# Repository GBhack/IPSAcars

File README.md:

# IPSAcars : Evolution de véhicules autonomes dans un environnement urbain intelligent

## Description du projet :
Réalisation une maquette simulant un environement urbain comprenant des feux de signalisation "intelligents" (c´est à dire s´adaptant à la circulation) à l´ aide d´ une carte FPGA et, dans le même temps, des véhicules autonomes (à l´ aide d'un BeagleBone) capables de circuler dans cet environnement.

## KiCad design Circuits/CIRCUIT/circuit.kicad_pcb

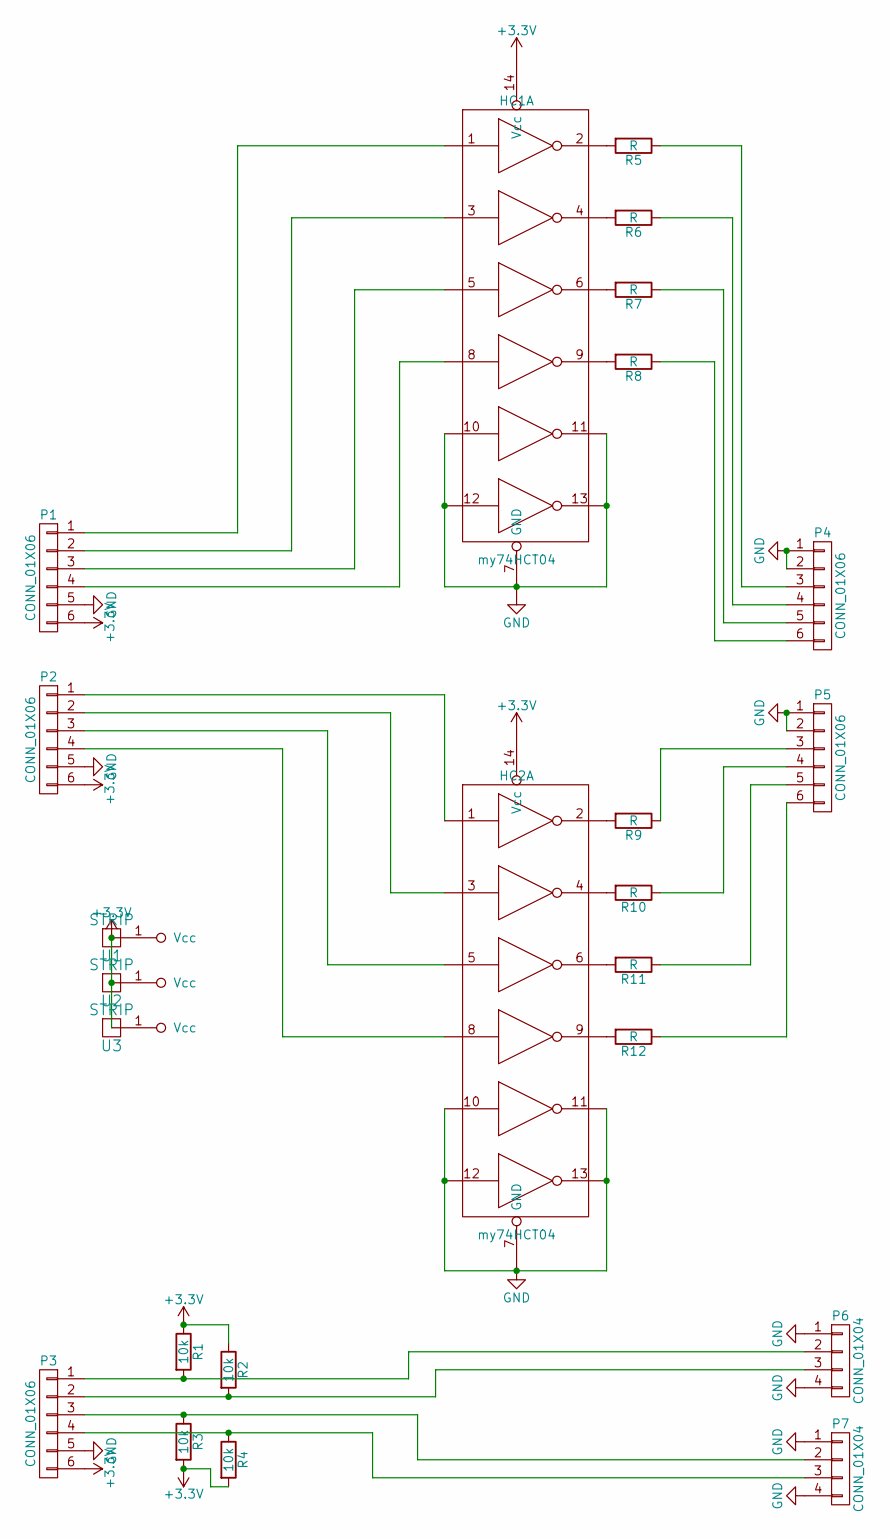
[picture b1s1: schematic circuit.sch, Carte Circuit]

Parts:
HC1, HC2: my74HCT04; DIP-14_W7.62mm
P1, P2, P3, P4, P5: CONN_01X06; Pin_Header_Angled_1x06
P6, P7: CONN_01X04; Pin_Header_Straight_1x04
R1, R2, R3, R4: 10k; Resistor_Horizontal_RM7mm
R5, R6, R7, R8, R9, R10, R11, R12: R; Resistor_Horizontal_RM7mm
U1, U2, U3: STRIP; SolderWirePad_2x_1-2mmDrill

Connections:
GND: HC1.7 (GND), HC2.7 (GND), HC2.10, HC2.11, HC2.12, HC2.13, P1.5, P2.5, P3.5, P4.1, P4.2, P5.1, P5.2, P6.1, P6.4, P7.1, P7.4
unnamed: HC1.1, P1.1
unnamed: HC1.2, R5.2
unnamed: HC1.3, P1.2
unnamed: HC1.4, R6.2
unnamed: HC1.5, P1.3
unnamed: HC1.6, R7.2
unnamed: HC1.8, P1.4
unnamed: HC1.9, R8.2
unnamed: HC1.10, HC1.11, HC1.12, HC1.13
unnamed: HC2.1, P2.1
unnamed: HC2.2, R9.2
unnamed: HC2.3, P2.2
unnamed: HC2.4, R10.2
unnamed: HC2.5, P2.3
unnamed: HC2.6, R11.2
unnamed: HC2.8, P2.4
unnamed: HC2.9, R12.2
unnamed: P3.1, P6.2, R1.2
unnamed: P3.2, P6.3, R2.2
unnamed: P3.3, P7.2, R3.1
unnamed: P3.4, P7.3, R4.1
unnamed: P4.3, R5.1
unnamed: P4.4, R6.1
unnamed: P4.5, R7.1
unnamed: P4.6, R8.1
unnamed: P5.3, R9.1
unnamed: P5.4, R10.1
unnamed: P5.5, R11.1
unnamed: P5.6, R12.1

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
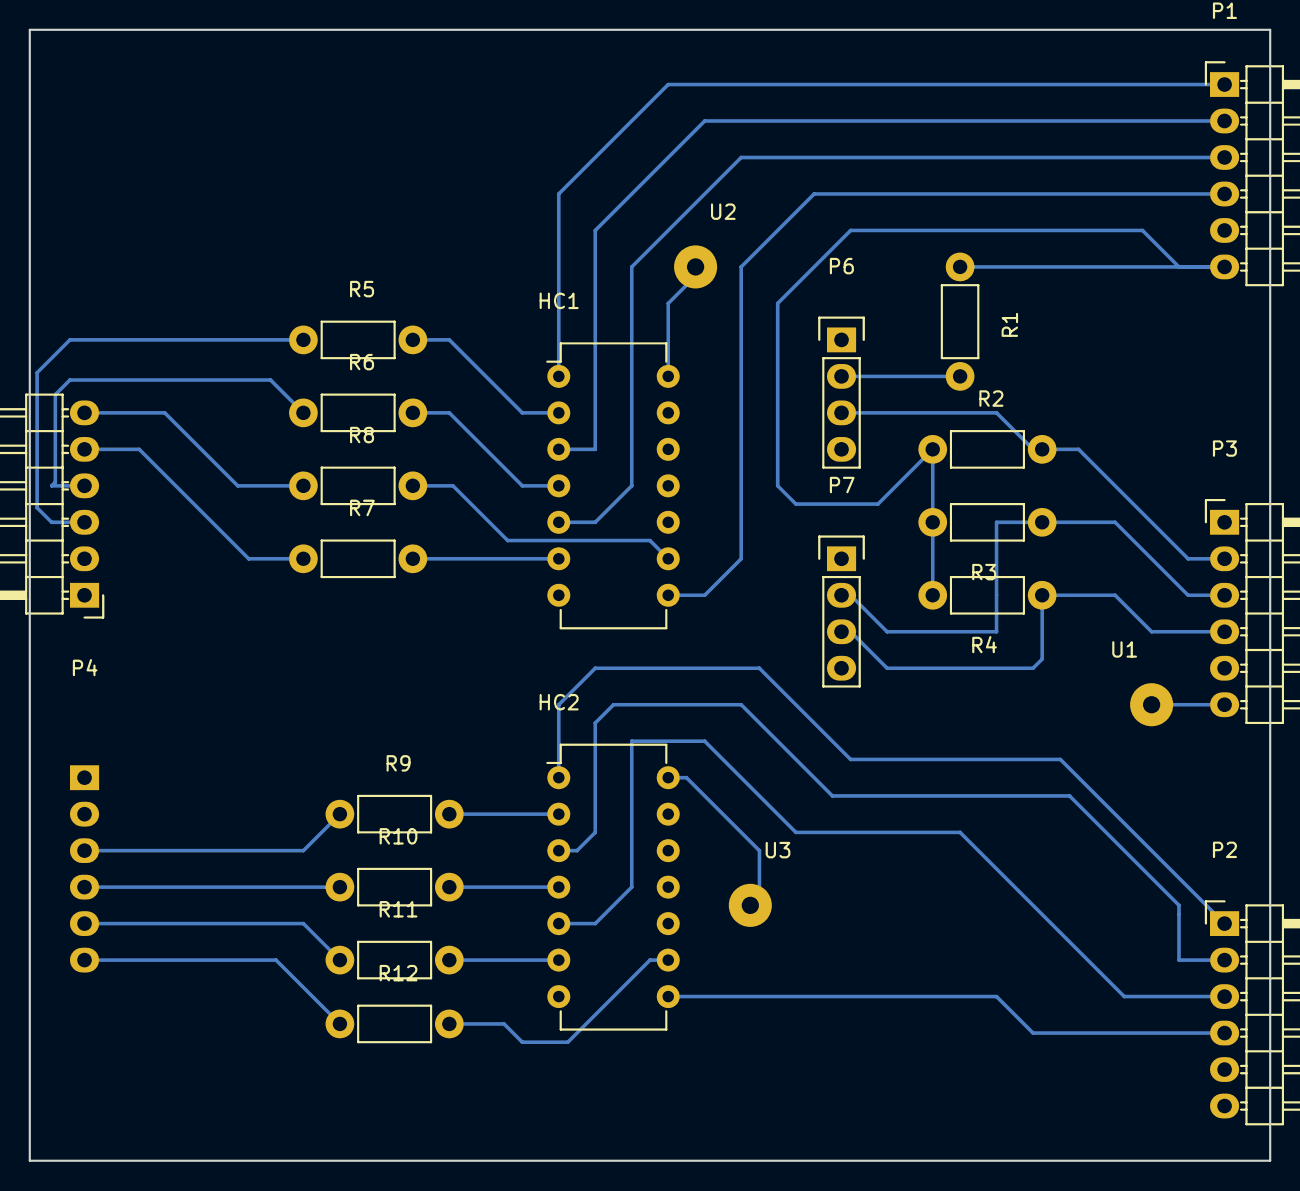
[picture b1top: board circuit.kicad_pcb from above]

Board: 2 copper layers, 86.4 x 78.7 mm, 24 parts (1 on the bottom side), 32 nets.

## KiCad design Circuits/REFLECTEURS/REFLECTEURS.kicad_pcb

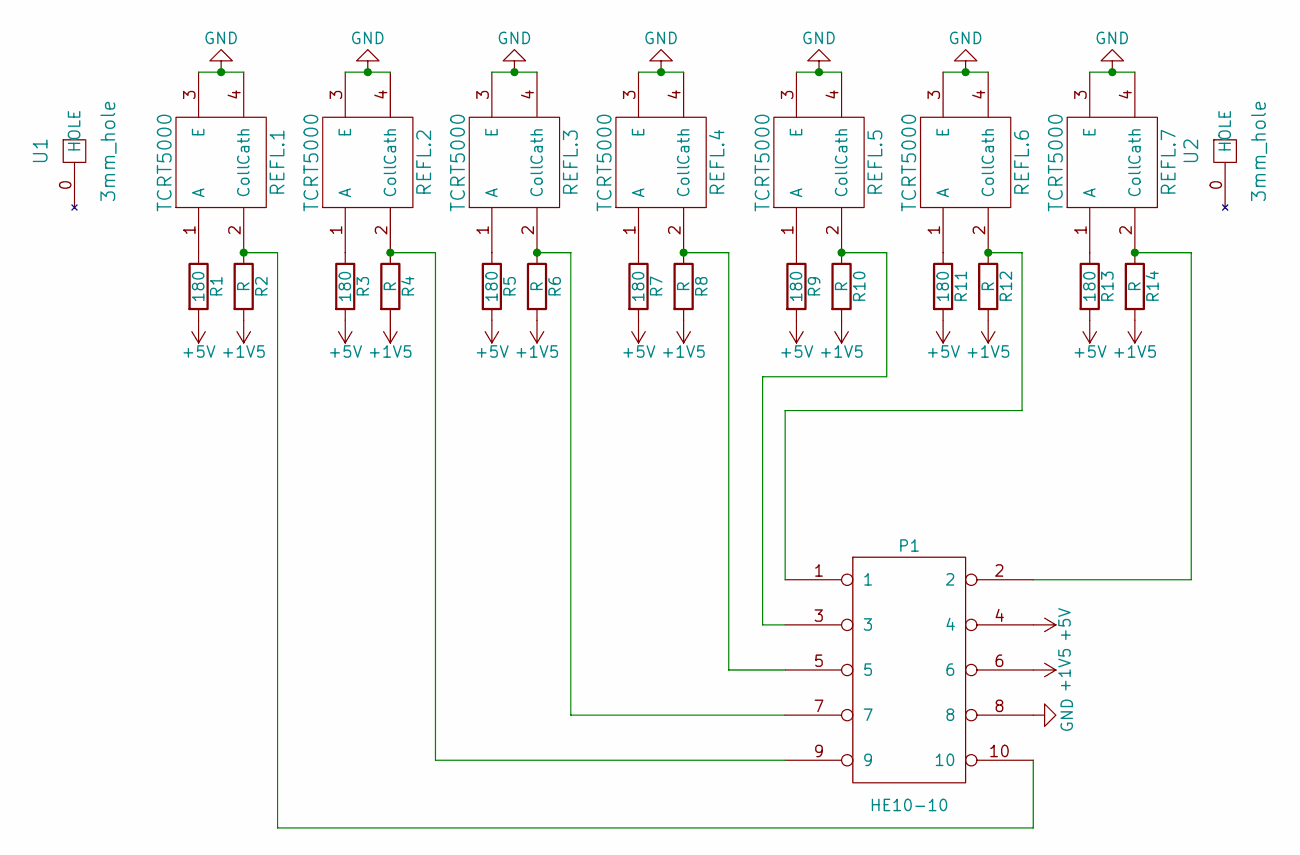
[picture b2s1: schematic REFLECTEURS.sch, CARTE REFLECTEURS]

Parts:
P1: HE10-10
R1, R3, R5, R7, R9, R11, R13: 180; Resistor_Horizontal_RM7mm
R2, R4, R6, R8, R10, R12, R14: R; Resistor_Horizontal_RM7mm
REFL.1, REFL.2, REFL.3, REFL.4, REFL.5, REFL.6, REFL.7: TCRT5000; TRCT5000
U1, U2: 3mm_hole; 3mmHOLE

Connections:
+1V5: P1.6, R2.2, R4.2, R6.2, R8.2, R10.2, R12.2, R14.2
+5V: P1.4, R1.2, R3.2, R5.2, R7.2, R9.2, R11.2, R13.2
GND: P1.8, REFL.1.3 (E), REFL.1.4 (Cath), REFL.2.3 (E), REFL.2.4 (Cath), REFL.3.3 (E), REFL.3.4 (Cath), REFL.4.3 (E), REFL.4.4 (Cath), REFL.5.3 (E), REFL.5.4 (Cath), REFL.6.3 (E), REFL.6.4 (Cath), REFL.7.3 (E), REFL.7.4 (Cath)
unnamed: P1.1, R12.1, REFL.6.2 (Coll)
unnamed: P1.2, R14.1, REFL.7.2 (Coll)
unnamed: P1.3, R10.1, REFL.5.2 (Coll)
unnamed: P1.5, R8.1, REFL.4.2 (Coll)
unnamed: P1.7, R6.1, REFL.3.2 (Coll)
unnamed: P1.9, R4.1, REFL.2.2 (Coll)
unnamed: P1.10, R2.1, REFL.1.2 (Coll)
unnamed: R1.1, REFL.1.1 (A)
unnamed: R3.1, REFL.2.1 (A)
unnamed: R5.1, REFL.3.1 (A)
unnamed: R7.1, REFL.4.1 (A)
unnamed: R9.1, REFL.5.1 (A)
unnamed: R11.1, REFL.6.1 (A)
unnamed: R13.1, REFL.7.1 (A)

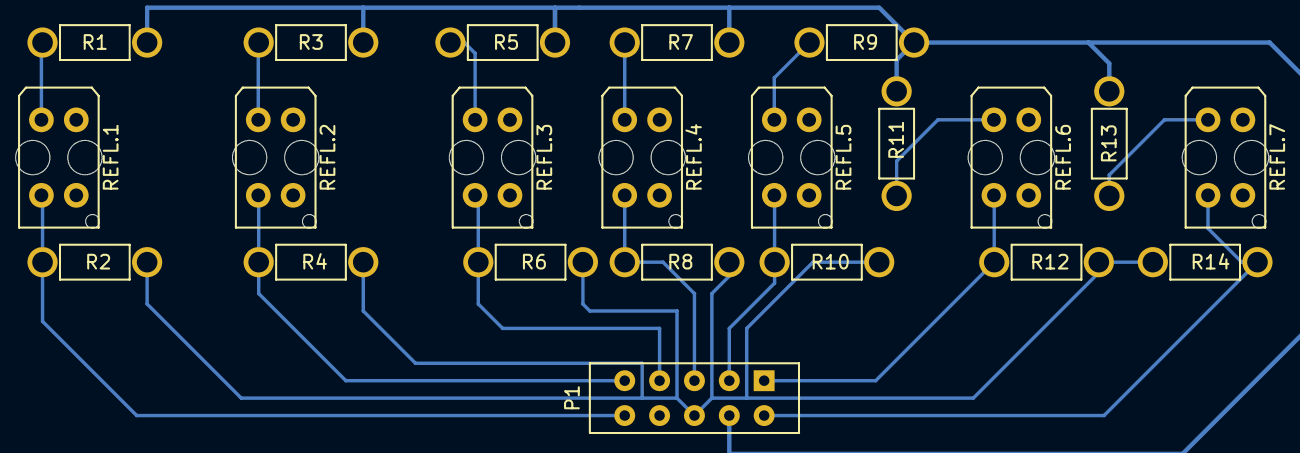
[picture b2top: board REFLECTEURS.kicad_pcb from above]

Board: 2 copper layers, 24 parts (0 on the bottom side), 17 nets.

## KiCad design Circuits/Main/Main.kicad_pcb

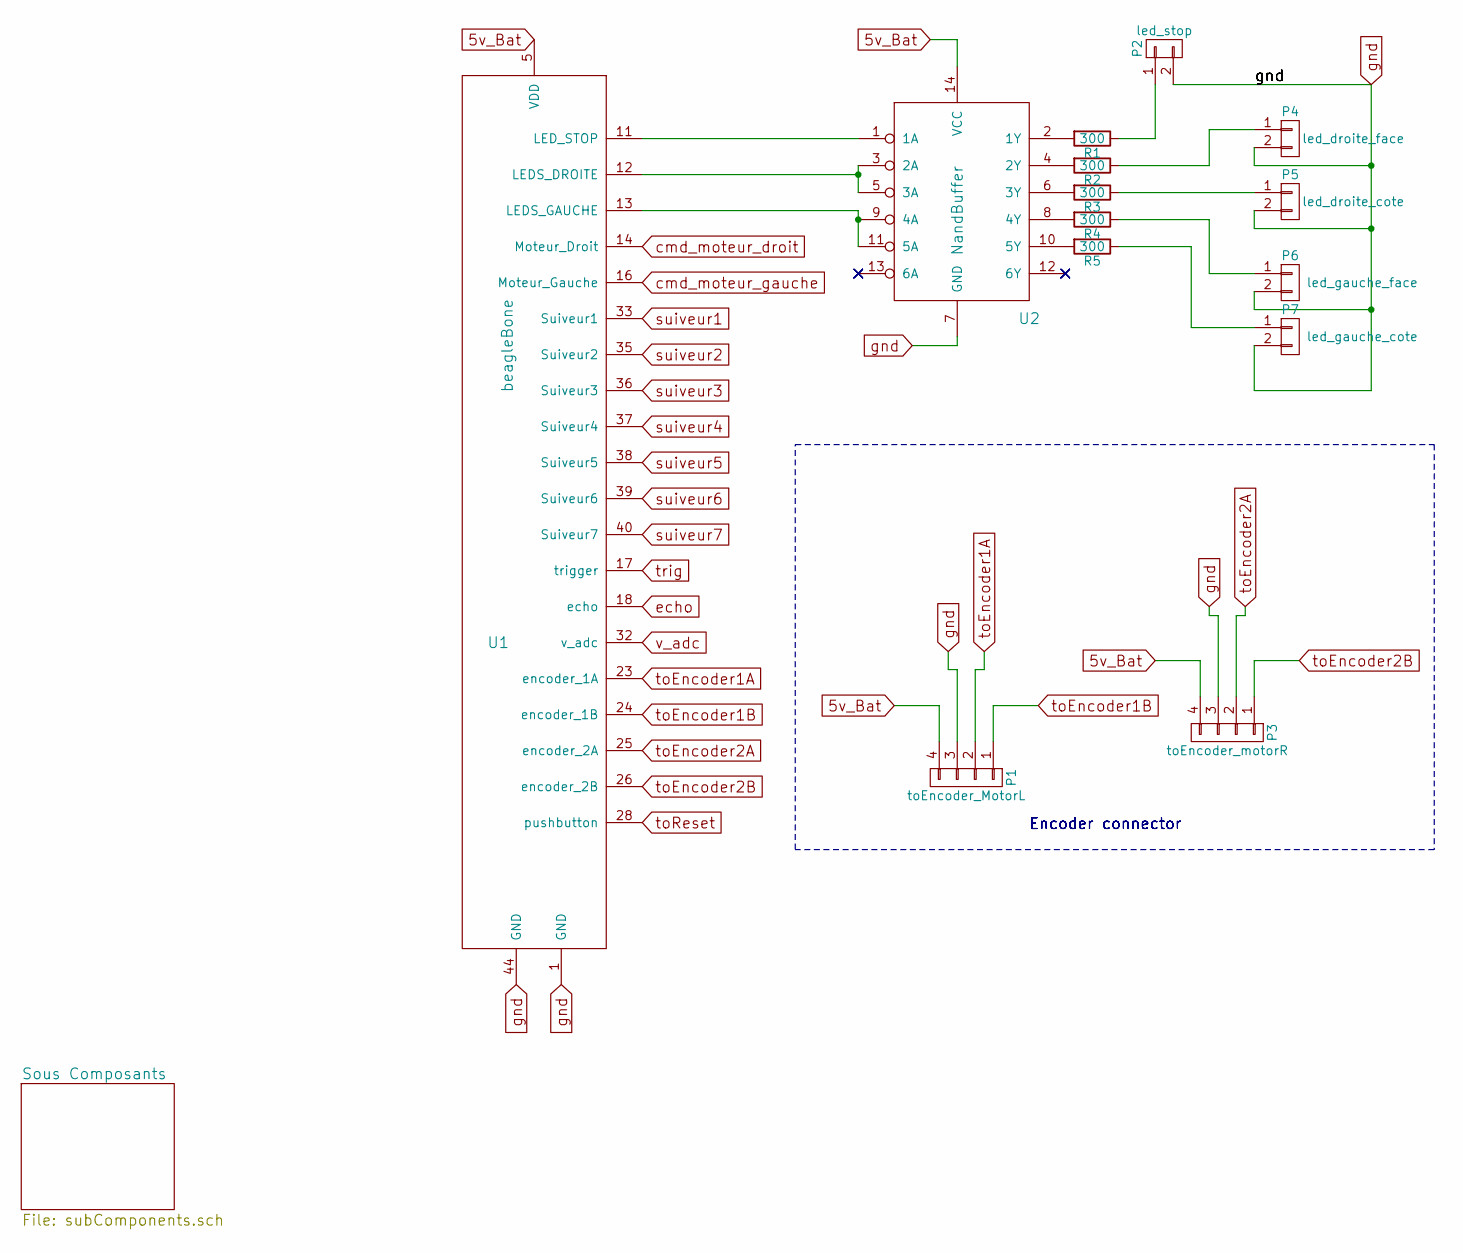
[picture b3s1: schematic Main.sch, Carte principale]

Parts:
P1: toEncoder_MotorL; Pin_Header_Straight_1x04
P2: led_stop; Pin_Header_Straight_1x02
P3: toEncoder_motorR; Pin_Header_Straight_1x04
P4: led_droite_face; Pin_Header_Straight_1x02
P5: led_droite_cote; Pin_Header_Straight_1x02
P6: led_gauche_face; Pin_Header_Straight_1x02
P7: led_gauche_cote; Pin_Header_Straight_1x02
R1, R2, R3, R4, R5: 300; Resistor_Horizontal_RM10mm
U1: beagleBone; beagleBoneGRNFootPrint
U2: NandBuffer

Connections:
5v_Bat: P1.4, P3.4, U1.5 (VDD), U2.14 (VCC); also elsewhere on the board
unnamed: P2.1, R1.1
unnamed: P4.1, R2.1
unnamed: P5.1, R3.1
unnamed: P6.1, R4.1
unnamed: P7.1, R5.1
unnamed: R1.2, U2.2 (1Y)
unnamed: R2.2, U2.4 (2Y)
unnamed: R3.2, U2.6 (3Y)
unnamed: R4.2, U2.8 (4Y)
unnamed: R5.2, U2.10 (5Y)
unnamed: U1.11 (LED_STOP), U2.1 (1A)
unnamed: U1.12 (LEDS_DROITE), U2.3 (2A), U2.5 (3A)
unnamed: U1.13 (LEDS_GAUCHE), U2.9 (4A), U2.11 (5A)
cmd_moteur_droit: U1.14 (Moteur_Droit); also elsewhere on the board
cmd_moteur_gauche: U1.16 (Moteur_Gauche); also elsewhere on the board
echo: U1.18 (echo); also elsewhere on the board
gnd: P1.3, P2.2, P3.3, P4.2, P5.2, P6.2, P7.2, U1.1 (GND), U1.44 (GND), U2.7 (GND); also elsewhere on the board
suiveur1: U1.33 (Suiveur1); also elsewhere on the board
suiveur2: U1.35 (Suiveur2); also elsewhere on the board
suiveur3: U1.36 (Suiveur3); also elsewhere on the board
suiveur4: U1.37 (Suiveur4); also elsewhere on the board
suiveur5: U1.38 (Suiveur5); also elsewhere on the board
suiveur6: U1.39 (Suiveur6); also elsewhere on the board
suiveur7: U1.40 (Suiveur7); also elsewhere on the board
toEncoder1A: P1.2, U1.23 (encoder_1A)
toEncoder1B: P1.1, U1.24 (encoder_1B)
toEncoder2A: P3.2, U1.25 (encoder_2A)
toEncoder2B: P3.1, U1.26 (encoder_2B)
toReset: U1.28 (pushbutton); also elsewhere on the board
trig: U1.17 (trigger); also elsewhere on the board
v_adc: U1.32 (v_adc); also elsewhere on the board

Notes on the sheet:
Encoder connector

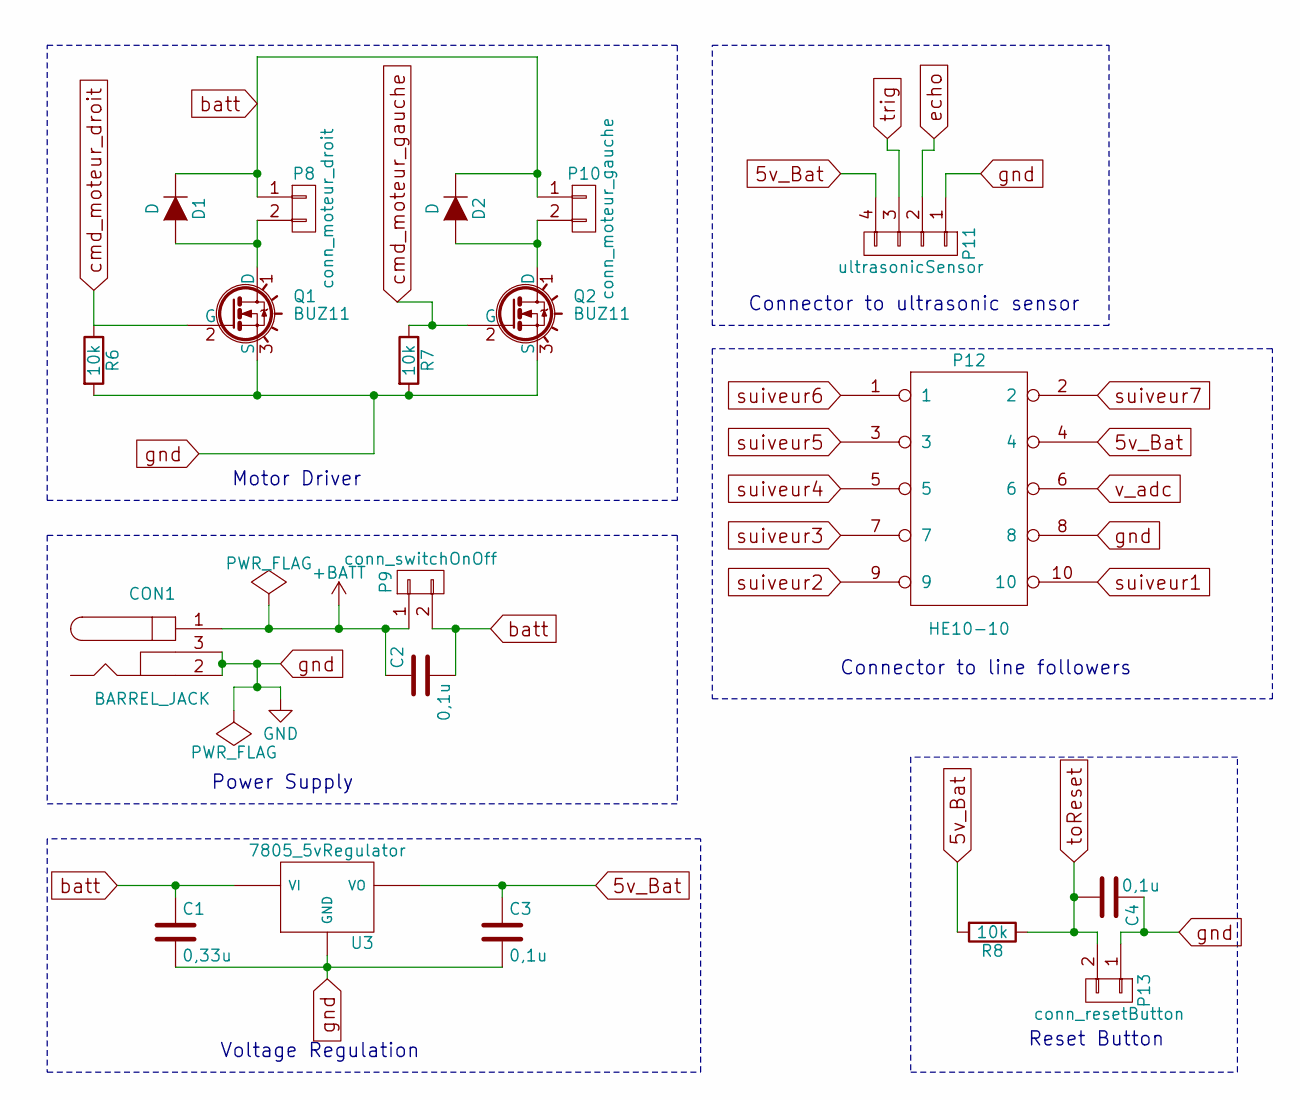
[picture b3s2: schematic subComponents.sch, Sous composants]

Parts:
C1: 0,33u; C_Disc_D3_P2.5
C2, C3, C4: 0,1u; C_Disc_D3_P2.5
CON1: BARREL_JACK
D1, D2: D; Diode_DO-35_SOD27_Horizontal_RM10
P8: conn_moteur_droit; Pin_Header_Straight_1x02
P9: conn_switchOnOff; Pin_Header_Straight_1x02
P10: conn_moteur_gauche; Pin_Header_Straight_1x02
P11: ultrasonicSensor; Pin_Header_Straight_1x04
P12: HE10-10; he10-10d
P13: conn_resetButton; Pin_Header_Straight_1x02
Q1, Q2: BUZ11; TO-220
R6, R7, R8: 10k; Resistor_Horizontal_RM10mm
U3: 7805_5vRegulator; voltageRegulator5v

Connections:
5v_Bat: C3.1, P11.4, P12.4, R8.2, U3.3 (VO); also elsewhere on the board
+BATT: C2.1, CON1.1, P9.1
unnamed: D1.2 (A), P8.2, Q1.1 (D)
unnamed: D2.2 (A), P10.2, Q2.1 (D)
batt: C1.1, C2.2, D1.1 (K), D2.1 (K), P8.1, P9.2, P10.1, U3.1 (VI)
cmd_moteur_droit: Q1.2 (G), R6.1; also elsewhere on the board
cmd_moteur_gauche: Q2.2 (G), R7.1; also elsewhere on the board
echo: P11.2; also elsewhere on the board
gnd: C1.2, C3.2, C4.1, CON1.2, CON1.3, P11.1, P12.8, P13.1, Q1.3 (S), Q2.3 (S), R6.2, R7.2, U3.2 (GND); also elsewhere on the board
suiveur1: P12.10; also elsewhere on the board
suiveur2: P12.9; also elsewhere on the board
suiveur3: P12.7; also elsewhere on the board
suiveur4: P12.5; also elsewhere on the board
suiveur5: P12.3; also elsewhere on the board
suiveur6: P12.1; also elsewhere on the board
suiveur7: P12.2; also elsewhere on the board
toReset: C4.2, P13.2, R8.1; also elsewhere on the board
trig: P11.3; also elsewhere on the board
v_adc: P12.6; also elsewhere on the board

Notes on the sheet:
Motor Driver
Connector to ultrasonic sensor
Power Supply
Reset Button
Connector to line followers
Voltage Regulation

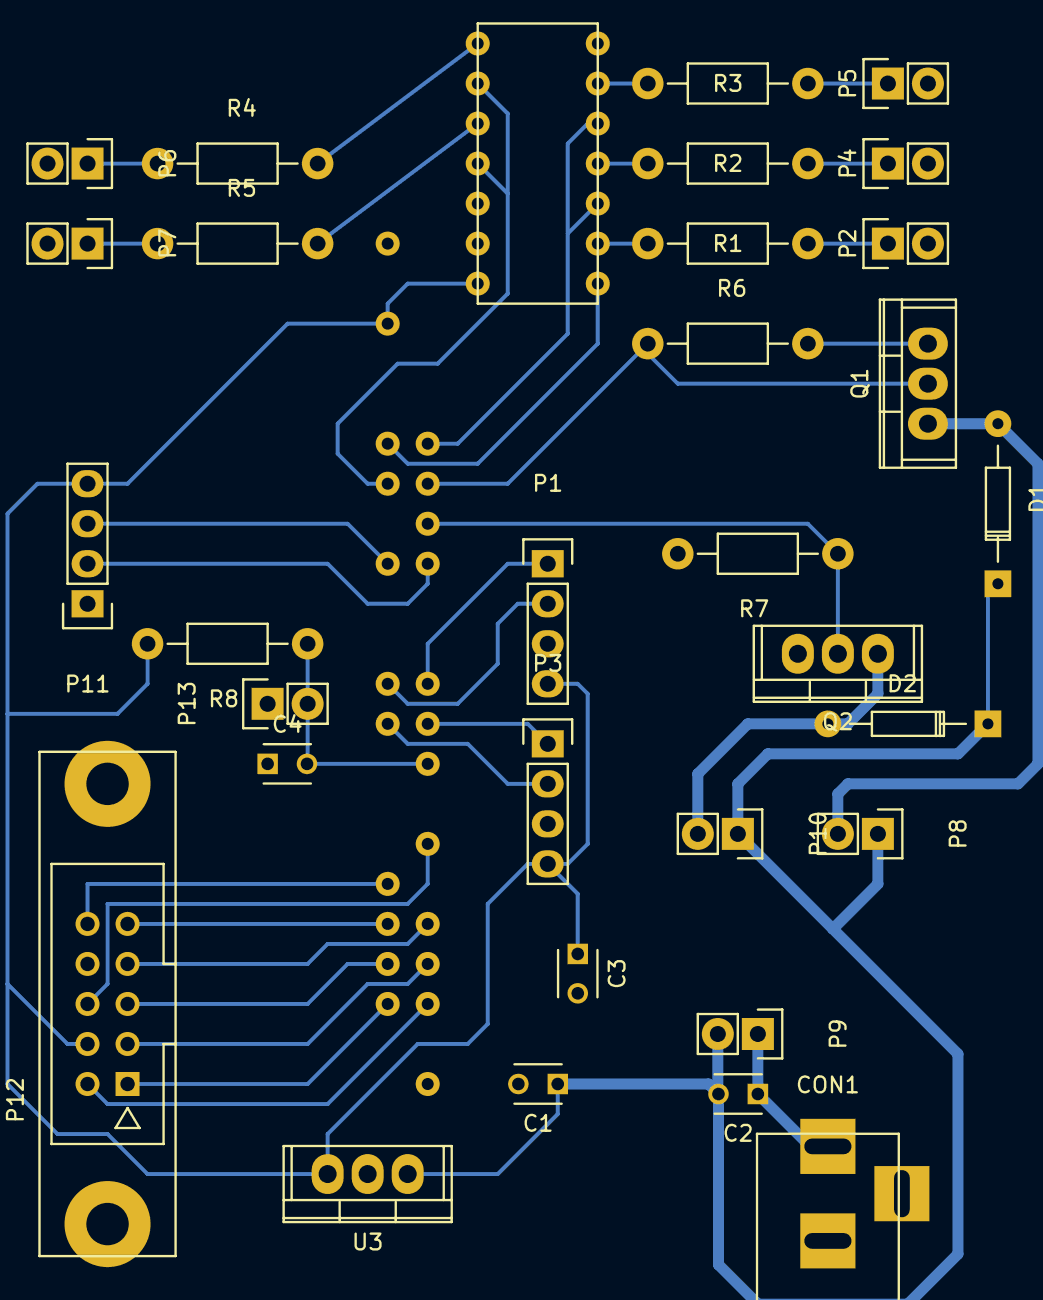
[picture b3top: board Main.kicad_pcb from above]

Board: 2 copper layers, 33 parts (0 on the bottom side), 36 nets.

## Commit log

2016-03-21 Ajout de la structure du rapport
2016-03-21 Ajout du readme
2016-03-22 Nouvelle structure de rapport
2016-04-11 Integration du plan final avec references et annexes
2016-04-19 MAJ du rapport
2016-05-12 Nouveau logo IPSA, nouvelles illustration et debut de solution de suivi de ligne
2016-05-16 Structure de dossiers plus clean, utilisation de projet Sublime-Text et ajout d'instructions de compilation LaTeX
2016-06-05 Tres gros changements sur l'ensemble
2016-06-06 Corrections et rédaction sur la partie 3
2016-06-06 Corrections du rapport + Carte Mère
2016-06-06 Carte mère
2016-06-06 correction figure 11
2016-06-06 Petites modifs
2016-06-06 Intégration ensemble propulsif ajouté
2016-06-07 Ajout paragraphes integration reflecteurs, structure et maquette
2016-06-07 Redimmensionnement des images matricielles
2016-06-08 MAJ biblio
2016-06-08 Redaction rapport - Partie 3
2016-06-08 Ajout de graphics
2016-06-08 Compilation des deux versions
2016-06-08 Ajout paragraphe Implementation logicielle
2016-06-09 Amelioration carte reflecteurs (simple face)
2016-06-09 Ajout de la carte principale (schemas + gerbers) et intégration
2016-06-09 Ameliorations cartes + rapport
2016-06-09 Redaction Reconnaissance d'image + MaJ Schemas/gerbers
2016-06-09 Ajout partie couts
2016-06-09 Ajout parties Camille
2016-06-09 Redaction rapport - Reconnaissance d'image
2016-06-09 Corrections Rapport + Ajouts avant dodo
2016-06-10 Reconnaissance d'image + Abstract + Corrections diverses + Detections
2016-06-10 Integration Carte mère + Corrections diverses
2016-06-10 Ajout de la partie carte circuit
2016-06-10 Ajout de la partie moteur
2016-06-10 Petites rectifications demandees par mon loulou
2016-06-10 final
2016-06-10 Corrections
2016-06-10 Petites corrections
